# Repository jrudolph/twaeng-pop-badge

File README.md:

# Twäng POP! Badge

These are [KiCad](https://www.kicad.org/) sources from which the [Twäng](https://twaeng.de) [pop!](https://twaeng.de/musik/pop) badge was produced. This
is basically version 2 of the blinky sign described [on the blog](https://blog.virtual-void.net/2022/06/17/creating-a-blinky-sign-for-twaeng/).

The updated firmware can be built from the `pop-badge` branch of the [firmware repository](https://github.com/jrudolph/twaeng-pop-sign/tree/pop-badge).

## Schematics

The idea was to keep the basic original design based around a RPi Pico and WS2812b LEDs. For space and
cost reasons the amount of WS2812 LEDs was reduced to 25 and the smaller variant was chosen.

Additionally, 50 simple white LEDs were
added as a frame for the sign. These LEDs can not be controlled individually but only as the whole set. The brightness can be set by choosing appropriate PWM settings. 50 LEDs could consume 1A of
current which is a lot and cannot be sourced from a microcontroller pin directly. Since this was my first
electronics design, I was not totally certain how to set this up properly, so I went with a design, where I put both an NPN-transistor and an N-channel MOSFET on the board configurable via solder
jumpers. (It wasn't clear to me how much current the NPN transistor would really need to switch on all those 50 LEDs. The current gain might be enough to drive those but I wasn't sure what it would mean under PWM and under how much strain it would put the output pin of the Pico.)

I also put a debug header on the board for easy testing of components without requiring to
immediately solder the RPi Pico.

The Pico itself is soldered to the back using its castellated edges. The idea is here, to piggy-back
on the proven design of the Pico and avoid experimenting with a full-fledged MCU design. The Pico has a very flexible input power design based on a switching buck/boost converter, so you can either run via USB or any other power source like AA batteries within a wide range of voltages.

The LED setup is schematically simple:

RGB LEDs:

White LEDs:

## PCB

The PCB has the outline of speech bubble in the form of a star. It uses a two layer design
with most of the back being the ground plane with a small amount of via connections.

On the front are all the LEDs with the required support components. The white LEDs are switched on the low-side (via the N-channel MOSFET), so the outer frame is a fill which goes to the source of the MOSFET. I read that having loops on a PCB will more likely act as an antenna, so I spared out a bit of the fill in the upper-right corner. The anode of the LEDs is directly connected to 5V. The MOSFET is controlled via a MCU pin, using PWM to dim the LEDs. They will never be driven with full power, which would use `50 x 20mA = 1A` (and would be even more blindingly bright).

Here's KiCad's 3D rendering of the front:

On the back there is room to solder the Pico itself to the board, and an electrolytic capacitor to relieve the power source (but it also works reliably without), so I didn't actually place them. I left a half-circle cutout where the USB port of the Pico would be to hopefully allow USB plugs to
fit in more easily. Unfortunately, the cutout is to small to accommodate all kinds of plugs. Some
plugs fit, some don't.

## Final Result

This is how the badges looked in their shiny black solder mask when I unpacked them after production.

Front:

Back:

A first test using after soldering the test headers showed an unexpected result:

The outer frame of LEDs was red but I had ordered white LEDs instead (and also selected the
current limiting resistors based on the white LEDs' specs). After some back and forth, it turned
indeed out to be a production mistake. After quite some discussion, finally the production cost
was waived, I was happy about that even if the visual effect was not quite as intended.

After soldering the Pico to the back, I started [adapting the firmware](https://github.com/jrudolph/twaeng-pop-sign/compare/main...pop-badge) to the new layout. The number of
LEDs had to be adapted and I also created a new rainbow wave animation. This required to
know the position of the RGB LEDs, which [could be extracted](pop-badge/extract-pos.scala) from the placement files that
were needed for the production assembly.

and finally the new version came alive:

Here are old and new version next to each other:

All of the LEDs are blindingly bright, so I experimented with different kinds of sheets to put in
front to diffuse the light a bit and take a bit away from the brightness. The final setup was placed in a small frame behind a sheet of diffusing paper and is now powered with 3 AA batteries (which is also safer than a solution powered by lithium batteries).

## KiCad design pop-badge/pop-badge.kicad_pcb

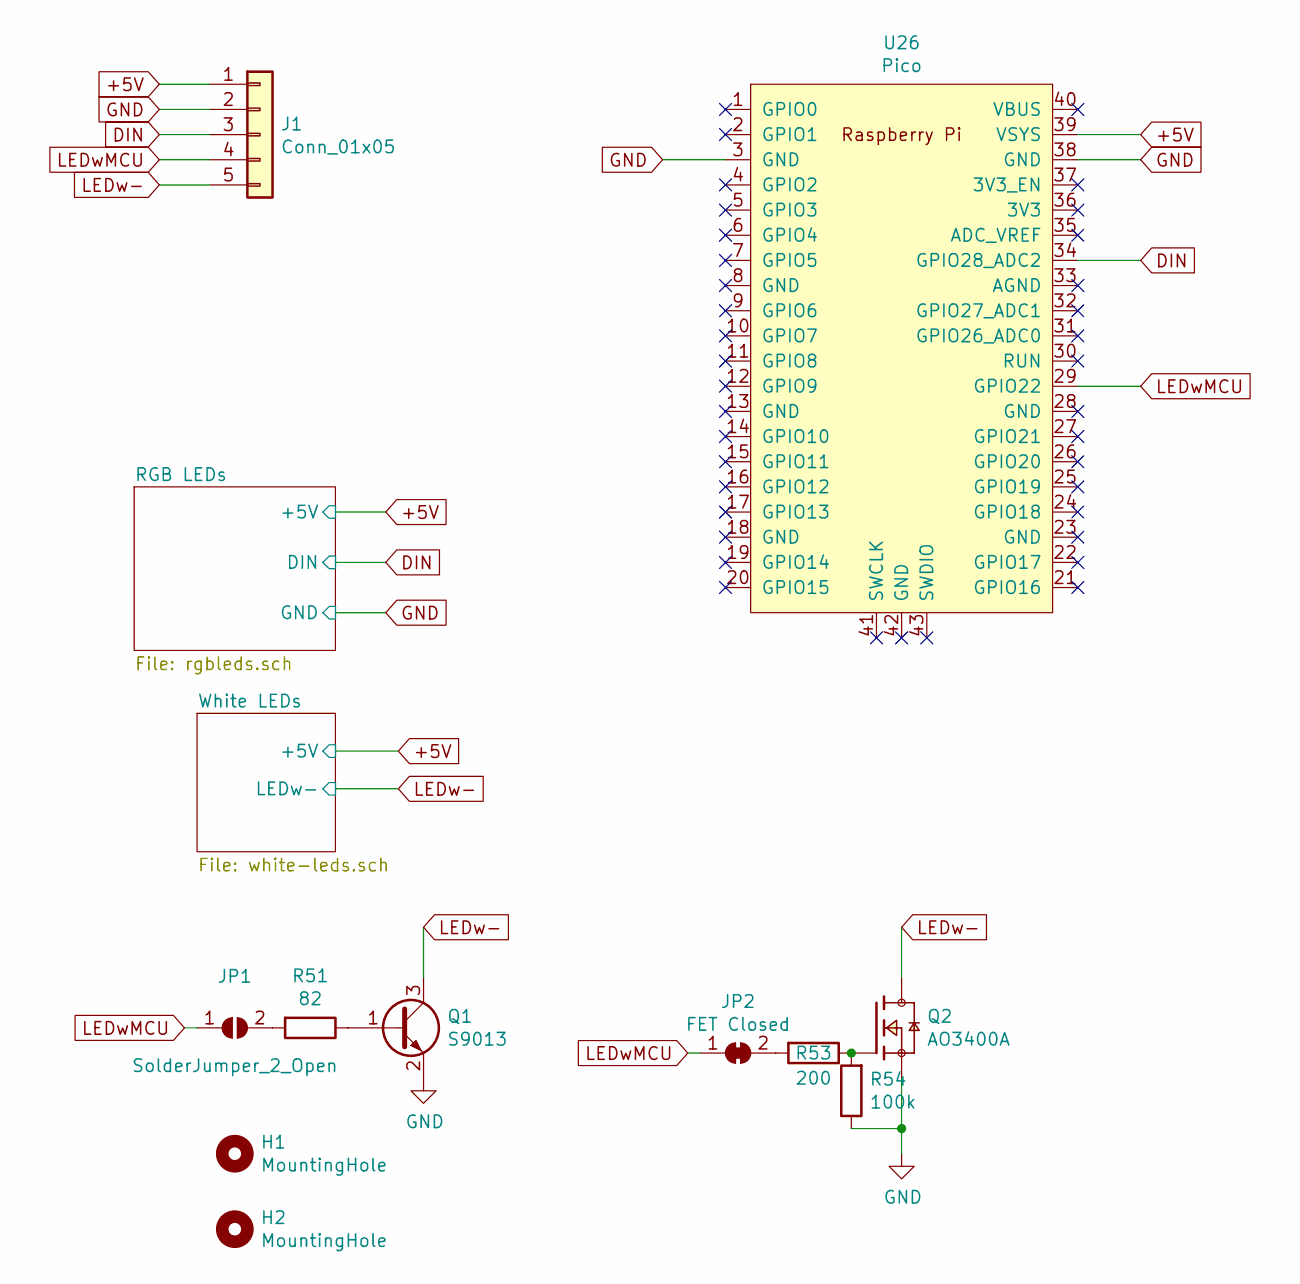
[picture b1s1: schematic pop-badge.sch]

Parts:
H1, H2: MountingHole; MountingHole_4.3mm_M4
J1: Conn_01x05; PinHeader_1x05_P2.54mm_Vertical
JP1: SolderJumper_2_Open; SolderJumper-2_P1.3mm_Open_Pad1.0x1.5mm
JP2: FET Closed; SolderJumper-2_P1.3mm_Bridged_Pad1.0x1.5mm
Q1: S9013; SOT-23_Handsoldering; JLC C6749
Q2: AO3400A; SOT95P280X125-3N; PARTREV L; JLC C20917
R51: 82; R_0603_1608Metric_Pad1.05x0.95mm_HandSolder; JLC 0603
R53: 200; R_0603_1608Metric_Pad1.05x0.95mm_HandSolder; JLC 0603
R54: 100k; R_0603_1608Metric_Pad1.05x0.95mm_HandSolder; JLC 0603
U26: Pico; RPi_Pico_SMD

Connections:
+5V: J1.1, U26.39 (VSYS); also elsewhere on the board
DIN: J1.3, U26.34 (GPIO28_ADC2); also elsewhere on the board
GND: J1.2, Q1.2 (E), Q2.2, R54.1, U26.3 (GND), U26.38 (GND); also elsewhere on the board
LEDw-: J1.5, Q1.3 (C), Q2.3; also elsewhere on the board
LEDwMCU: J1.4, JP1.1 (A), JP2.1 (A), U26.29 (GPIO22)
unnamed: JP1.2 (B), R51.2
unnamed: JP2.2 (B), R53.2
unnamed: Q1.1 (B), R51.1
unnamed: Q2.1, R53.1, R54.2

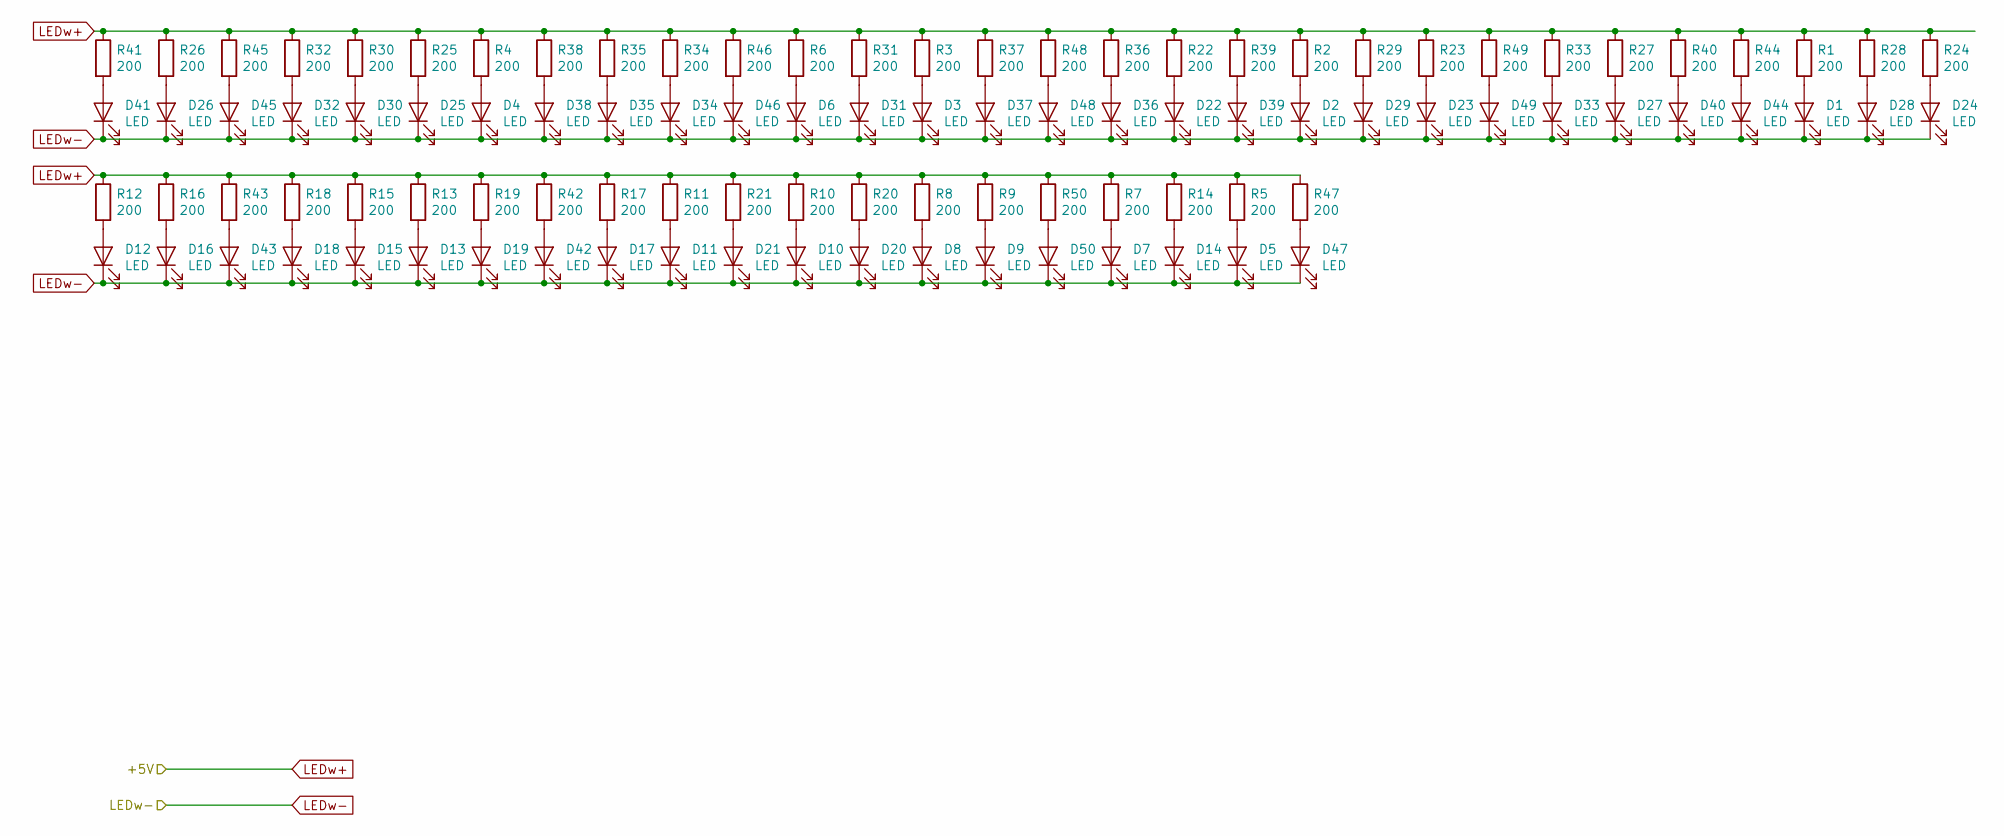
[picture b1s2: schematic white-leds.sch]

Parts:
D1, D2, D3, D4, D5, D6, D7, D8, D9, D10, D11, D12, D13, D14, D15, D16, D17, D18, D19, D20, D21, D22, D23, D24, D25, D26, D27, D28, D29, D30, D31, D32, D33, D34, D35, D36, D37, D38, D39, D40, D41, D42, D43, D44, D45, D46, D47, D48, D49, D50: LED; LED_0603_1608Metric; JLC C115461
R1, R2, R3, R4, R5, R6, R7, R8, R9, R10, R11, R12, R13, R14, R15, R16, R17, R18, R19, R20, R21, R22, R23, R24, R25, R26, R27, R28, R29, R30, R31, R32, R33, R34, R35, R36, R37, R38, R39, R40, R41, R42, R43, R44, R45, R46, R47, R48, R49, R50: 200; R_0603_1608Metric_Pad1.05x0.95mm_HandSolder; JLC 0603

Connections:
+5V: R1.1, R2.1, R3.1, R4.1, R5.1, R6.1, R7.1, R8.1, R9.1, R10.1, R11.1, R12.1, R13.1, R14.1, R15.1, R16.1, R17.1, R18.1, R19.1, R20.1, R21.1, R22.1, R23.1, R24.1, R25.1, R26.1, R27.1, R28.1, R29.1, R30.1, R31.1, R32.1, R33.1, R34.1, R35.1, R36.1, R37.1, R38.1, R39.1, R40.1, R41.1, R42.1, R43.1, R44.1, R45.1, R46.1, R47.1, R48.1, R49.1, R50.1; also elsewhere on the board
LEDw-: D1.1 (K), D2.1 (K), D3.1 (K), D4.1 (K), D5.1 (K), D6.1 (K), D7.1 (K), D8.1 (K), D9.1 (K), D10.1 (K), D11.1 (K), D12.1 (K), D13.1 (K), D14.1 (K), D15.1 (K), D16.1 (K), D17.1 (K), D18.1 (K), D19.1 (K), D20.1 (K), D21.1 (K), D22.1 (K), D23.1 (K), D24.1 (K), D25.1 (K), D26.1 (K), D27.1 (K), D28.1 (K), D29.1 (K), D30.1 (K), D31.1 (K), D32.1 (K), D33.1 (K), D34.1 (K), D35.1 (K), D36.1 (K), D37.1 (K), D38.1 (K), D39.1 (K), D40.1 (K), D41.1 (K), D42.1 (K), D43.1 (K), D44.1 (K), D45.1 (K), D46.1 (K), D47.1 (K), D48.1 (K), D49.1 (K), D50.1 (K); also elsewhere on the board
unnamed: D1.2 (A), R1.2
unnamed: D2.2 (A), R2.2
unnamed: D3.2 (A), R3.2
unnamed: D4.2 (A), R4.2
unnamed: D5.2 (A), R5.2
unnamed: D6.2 (A), R6.2
unnamed: D7.2 (A), R7.2
unnamed: D8.2 (A), R8.2
unnamed: D9.2 (A), R9.2
unnamed: D10.2 (A), R10.2
unnamed: D11.2 (A), R11.2
unnamed: D12.2 (A), R12.2
unnamed: D13.2 (A), R13.2
unnamed: D14.2 (A), R14.2
unnamed: D15.2 (A), R15.2
unnamed: D16.2 (A), R16.2
unnamed: D17.2 (A), R17.2
unnamed: D18.2 (A), R18.2
unnamed: D19.2 (A), R19.2
unnamed: D20.2 (A), R20.2
unnamed: D21.2 (A), R21.2
unnamed: D22.2 (A), R22.2
unnamed: D23.2 (A), R23.2
unnamed: D24.2 (A), R24.2
unnamed: D25.2 (A), R25.2
unnamed: D26.2 (A), R26.2
unnamed: D27.2 (A), R27.2
unnamed: D28.2 (A), R28.2
unnamed: D29.2 (A), R29.2
unnamed: D30.2 (A), R30.2
unnamed: D31.2 (A), R31.2
unnamed: D32.2 (A), R32.2
unnamed: D33.2 (A), R33.2
unnamed: D34.2 (A), R34.2
unnamed: D35.2 (A), R35.2
unnamed: D36.2 (A), R36.2
unnamed: D37.2 (A), R37.2
unnamed: D38.2 (A), R38.2
unnamed: D39.2 (A), R39.2
unnamed: D40.2 (A), R40.2
unnamed: D41.2 (A), R41.2
unnamed: D42.2 (A), R42.2
unnamed: D43.2 (A), R43.2
unnamed: D44.2 (A), R44.2
unnamed: D45.2 (A), R45.2
unnamed: D46.2 (A), R46.2
unnamed: D47.2 (A), R47.2
unnamed: D48.2 (A), R48.2
unnamed: D49.2 (A), R49.2
unnamed: D50.2 (A), R50.2

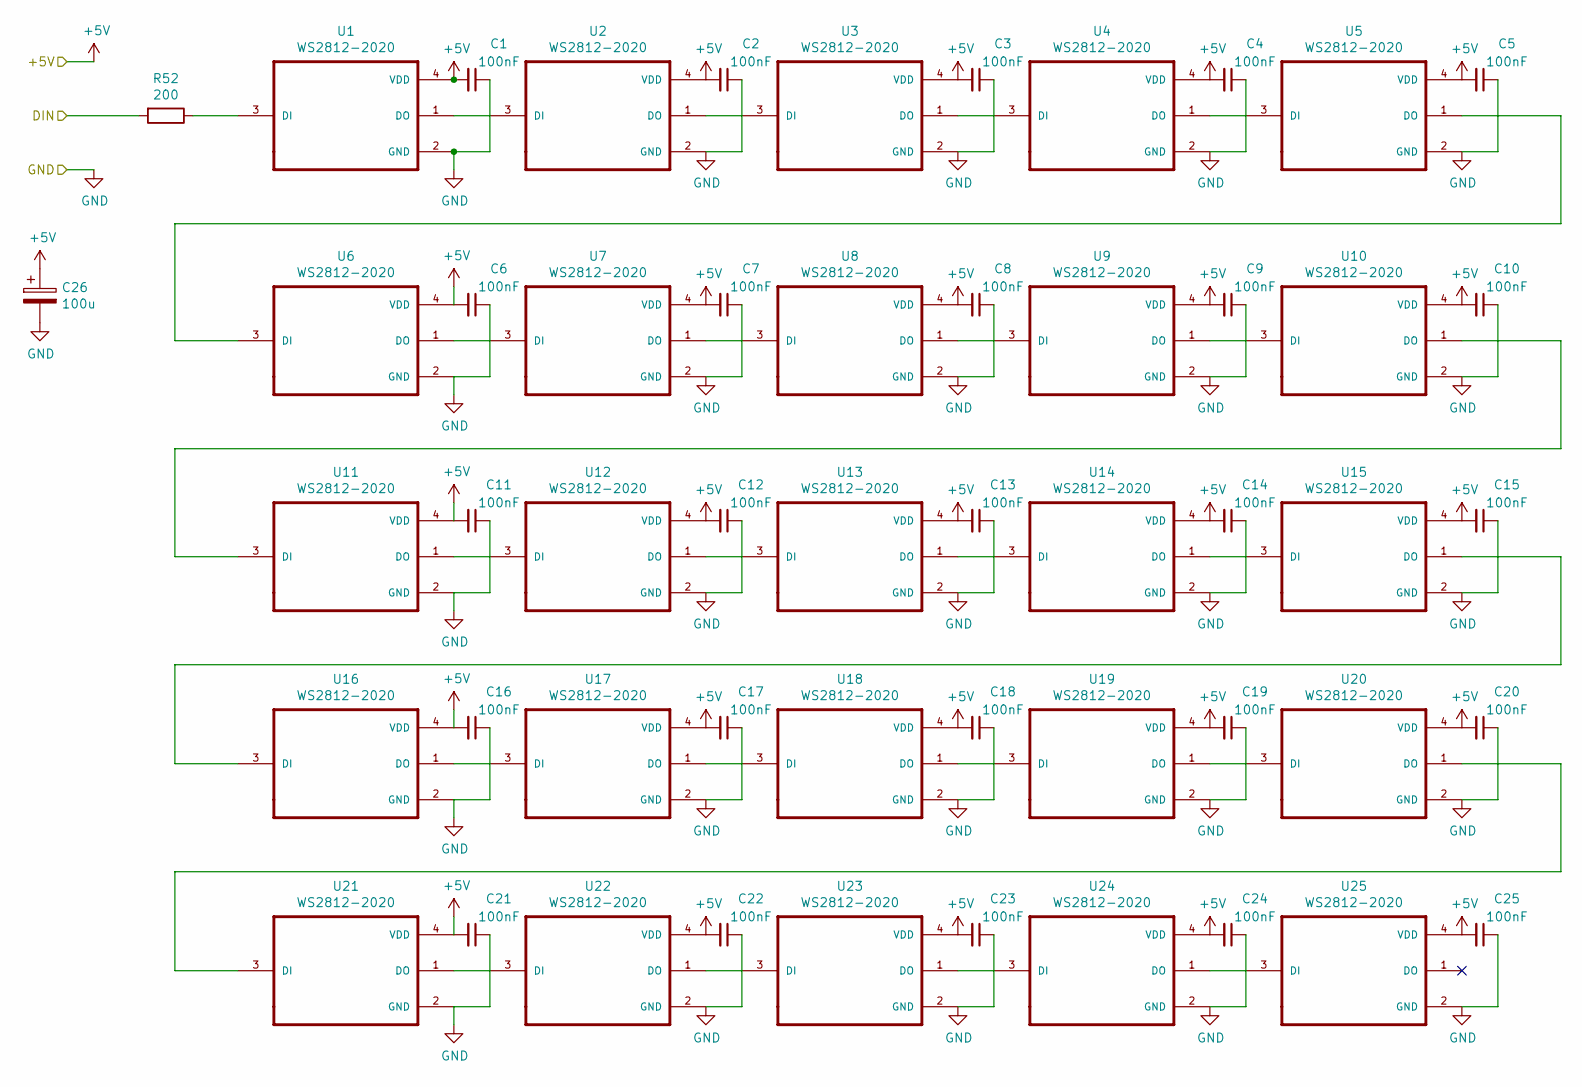
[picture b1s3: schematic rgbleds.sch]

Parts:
C1, C2, C3, C4, C5, C6, C7, C8, C9, C10, C11, C12, C13, C14, C15, C16, C17, C18, C19, C20, C21, C22, C23, C24, C25: 100nF; C_0402_1005Metric; JLC 0402
C26: 100u; CP_Radial_D6.3mm_P2.50mm
R52: 200; R_0603_1608Metric_Pad1.05x0.95mm_HandSolder; JLC 0603
U1, U2, U3, U4, U5, U6, U7, U8, U9, U10, U11, U12, U13, U14, U15, U16, U17, U18, U19, U20, U21, U22, U23, U24, U25: WS2812-2020; LED_WS2812-2020; JLC C965555

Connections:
+5V: C1.2, C2.2, C3.2, C4.2, C5.2, C6.2, C7.2, C8.2, C9.2, C10.2, C11.2, C12.2, C13.2, C14.2, C15.2, C16.2, C17.2, C18.2, C19.2, C20.2, C21.2, C22.2, C23.2, C24.2, C25.2, C26.1, U1.4 (VDD), U2.4 (VDD), U3.4 (VDD), U4.4 (VDD), U5.4 (VDD), U6.4 (VDD), U7.4 (VDD), U8.4 (VDD), U9.4 (VDD), U10.4 (VDD), U11.4 (VDD), U12.4 (VDD), U13.4 (VDD), U14.4 (VDD), U15.4 (VDD), U16.4 (VDD), U17.4 (VDD), U18.4 (VDD), U19.4 (VDD), U20.4 (VDD), U21.4 (VDD), U22.4 (VDD), U23.4 (VDD), U24.4 (VDD), U25.4 (VDD); also elsewhere on the board
DIN: R52.2; also elsewhere on the board
GND: C1.1, C2.1, C3.1, C4.1, C5.1, C6.1, C7.1, C8.1, C9.1, C10.1, C11.1, C12.1, C13.1, C14.1, C15.1, C16.1, C17.1, C18.1, C19.1, C20.1, C21.1, C22.1, C23.1, C24.1, C25.1, C26.2, U1.2 (GND), U2.2 (GND), U3.2 (GND), U4.2 (GND), U5.2 (GND), U6.2 (GND), U7.2 (GND), U8.2 (GND), U9.2 (GND), U10.2 (GND), U11.2 (GND), U12.2 (GND), U13.2 (GND), U14.2 (GND), U15.2 (GND), U16.2 (GND), U17.2 (GND), U18.2 (GND), U19.2 (GND), U20.2 (GND), U21.2 (GND), U22.2 (GND), U23.2 (GND), U24.2 (GND), U25.2 (GND); also elsewhere on the board
unnamed: R52.1, U1.3 (DI)
unnamed: U1.1 (DO), U2.3 (DI)
unnamed: U2.1 (DO), U3.3 (DI)
unnamed: U3.1 (DO), U4.3 (DI)
unnamed: U4.1 (DO), U5.3 (DI)
unnamed: U5.1 (DO), U6.3 (DI)
unnamed: U6.1 (DO), U7.3 (DI)
unnamed: U7.1 (DO), U8.3 (DI)
unnamed: U8.1 (DO), U9.3 (DI)
unnamed: U10.1 (DO), U11.3 (DI)
unnamed: U9.1 (DO), U10.3 (DI)
unnamed: U11.1 (DO), U12.3 (DI)
unnamed: U12.1 (DO), U13.3 (DI)
unnamed: U13.1 (DO), U14.3 (DI)
unnamed: U14.1 (DO), U15.3 (DI)
unnamed: U15.1 (DO), U16.3 (DI)
unnamed: U16.1 (DO), U17.3 (DI)
unnamed: U17.1 (DO), U18.3 (DI)
unnamed: U18.1 (DO), U19.3 (DI)
unnamed: U19.1 (DO), U20.3 (DI)
unnamed: U20.1 (DO), U21.3 (DI)
unnamed: U21.1 (DO), U22.3 (DI)
unnamed: U22.1 (DO), U23.3 (DI)
unnamed: U23.1 (DO), U24.3 (DI)
unnamed: U24.1 (DO), U25.3 (DI)

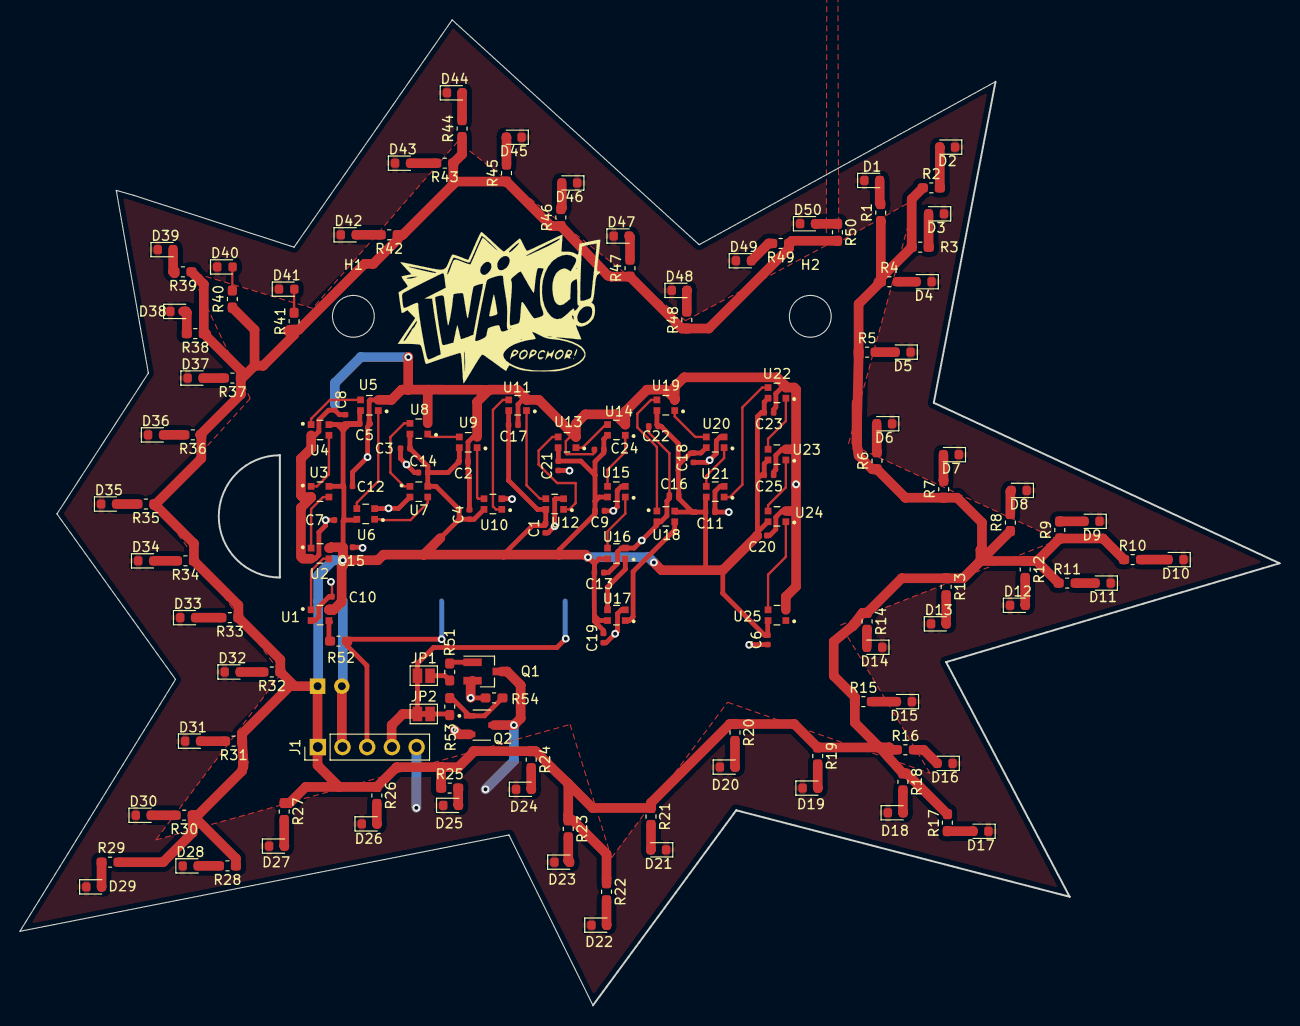
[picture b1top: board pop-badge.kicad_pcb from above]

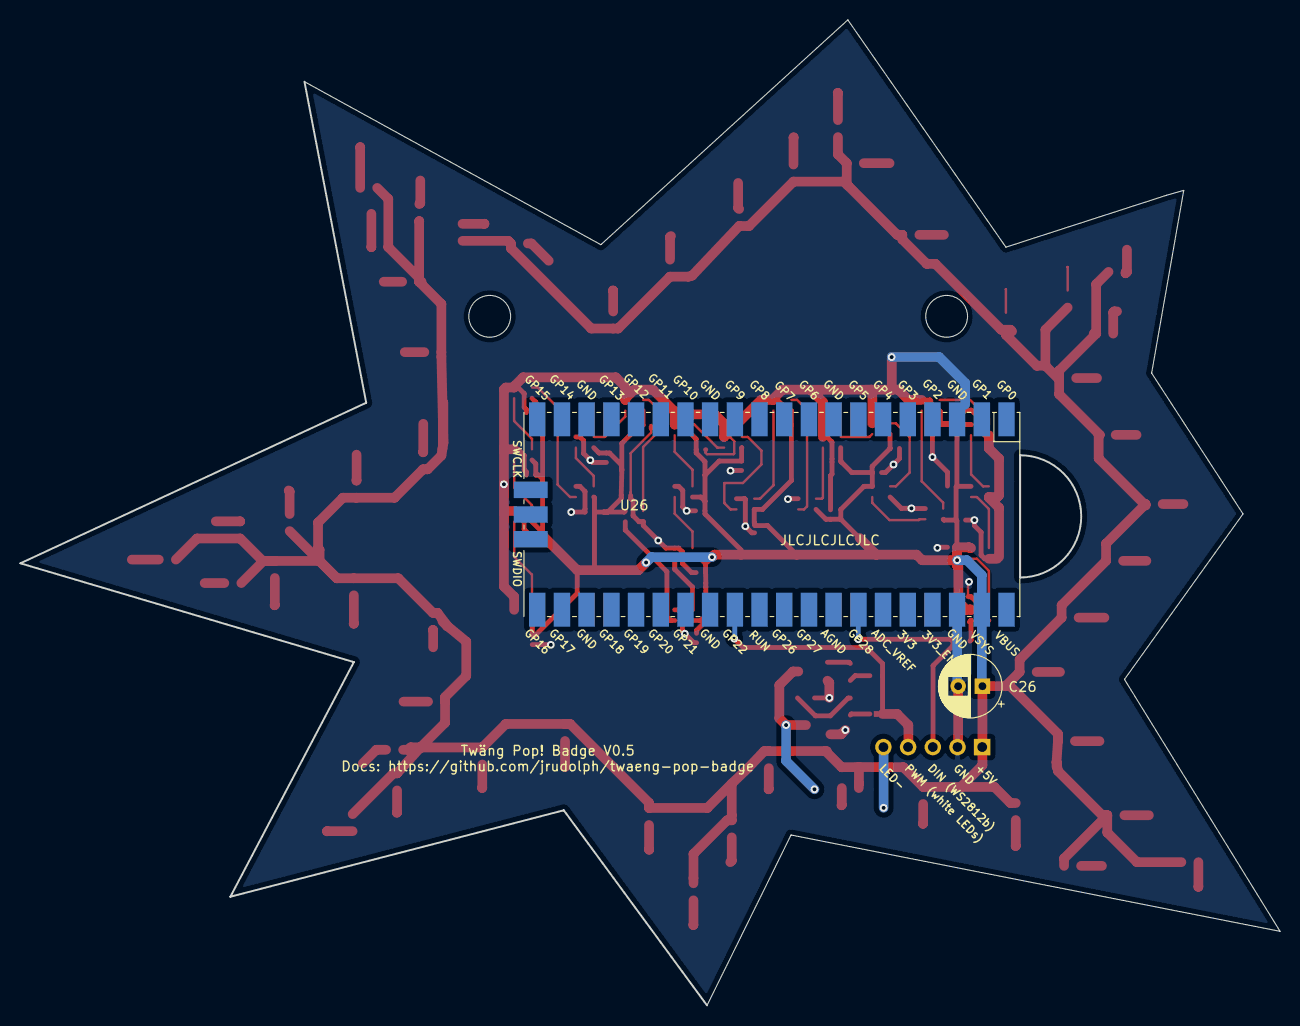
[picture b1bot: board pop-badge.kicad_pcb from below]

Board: 2 copper layers, 129.5 x 101.3 mm, 163 parts (2 on the bottom side), 84 nets.

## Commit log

2021-09-29 initial version
2021-09-29 much more layouting
2021-09-29 routing mostly done
2021-09-30 current state
2021-09-30 add WS2812B 2020 decoupling caps (100nF)
2021-09-30 annotate decoupling caps
2021-09-30 add decoupling cap footprints
2021-09-30 import decoupling caps and remove power lines for redo for ws2812
2021-09-30 routing done
2021-10-01 different BJT again
2021-10-01 add a cut out for the usb connector
2021-10-01 fix silk screen labels
2021-10-01 fix cut out vs traces
2021-10-01 silk screen fix
2021-10-01 small bom fixes
2021-10-01 use 200 ohm current limiting resistor for LED
    To have more headroom without bringing BJT to its limits.
    Calculation basis:
    V_CE 0.6V max
    LTW-C193SN5 10mA at 3.15V, from chart ~ 5mA at 3V
    7mA at 200 Ohm = 1.4V voltage drop
    worst case 5V - 0.5V - 1.4V = 3.1V ~ 7mA at LED according to LED IV chart
2021-10-01 redo power rails to avoid loops
2021-10-01 some silkscreen adjustments
2021-10-02 use proper pin connector and expose LEDw- on connector
2021-10-02 add twaeng sign
2021-10-02 add alternative path
2021-10-02 add pull down for mosfet
2021-10-02 slight tracking changes
2021-10-03 add button
2021-10-04 some cosmetic changes
2021-10-04 remove button again
2021-10-04 add rescue lib
2021-10-06 change footprint for npn slightly
2021-10-06 remove button label
2021-10-06 renumber white leds
2021-10-06 set smd attribute for ws2812bs
2021-11-17 script to extract positions of WS2812B LEDs from placement files
2023-04-19 add README and some images
2023-04-19 more documentation
2023-04-19 README improvements
